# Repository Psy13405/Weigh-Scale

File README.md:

# Custom Portable Weigh Scale

## Overview

Building a custom weigh scale to measure up to 20 kg with high precision. Using a load cell to measure weight and an ESP32C3 development board to send data wirelessly to connected devices and display on LCD module. Modeling the frame of weigh scale in CAD software to 3D print. Designing a PCB to integrate components and optimize space.

## Repository Contents

- `src/` — Source code
- `include/` - Header files for all submodules
- `CAD_Files/` — All CAD models and printable files
- `3D_Prints/` - STL files for physical parts
- `PCB/` - PCB schematic and layout file (in progress)

## Hardware and Software

Hardware: HX711 Amplifier Board, XIAO ESP32C3, Aluminum Bar-type Load Cell, USB Debug Cable, Jumper Wires, 2x M4 and 2x M5 hex screws\
Software: ESP-IDF in preferred configuration. Example: Setup through PlatformIO extension in VS Code\

## Building and Running

Solder load cell wires to HX711 board and use jumper wires to connect to ESP. 3D print test bed and force plate, and fasten them to the load cell with screws. Flash the source code to the ESP and inspect through serial monitor.

## Results

Currently, the load cell reliably measures weight up to 10 kg and sends data wirelessly via Bluetooth Low Energy (BLE). Next steps include integrating an LCD module, modeling the full frame, and finishing the PCB layout for fabrication.

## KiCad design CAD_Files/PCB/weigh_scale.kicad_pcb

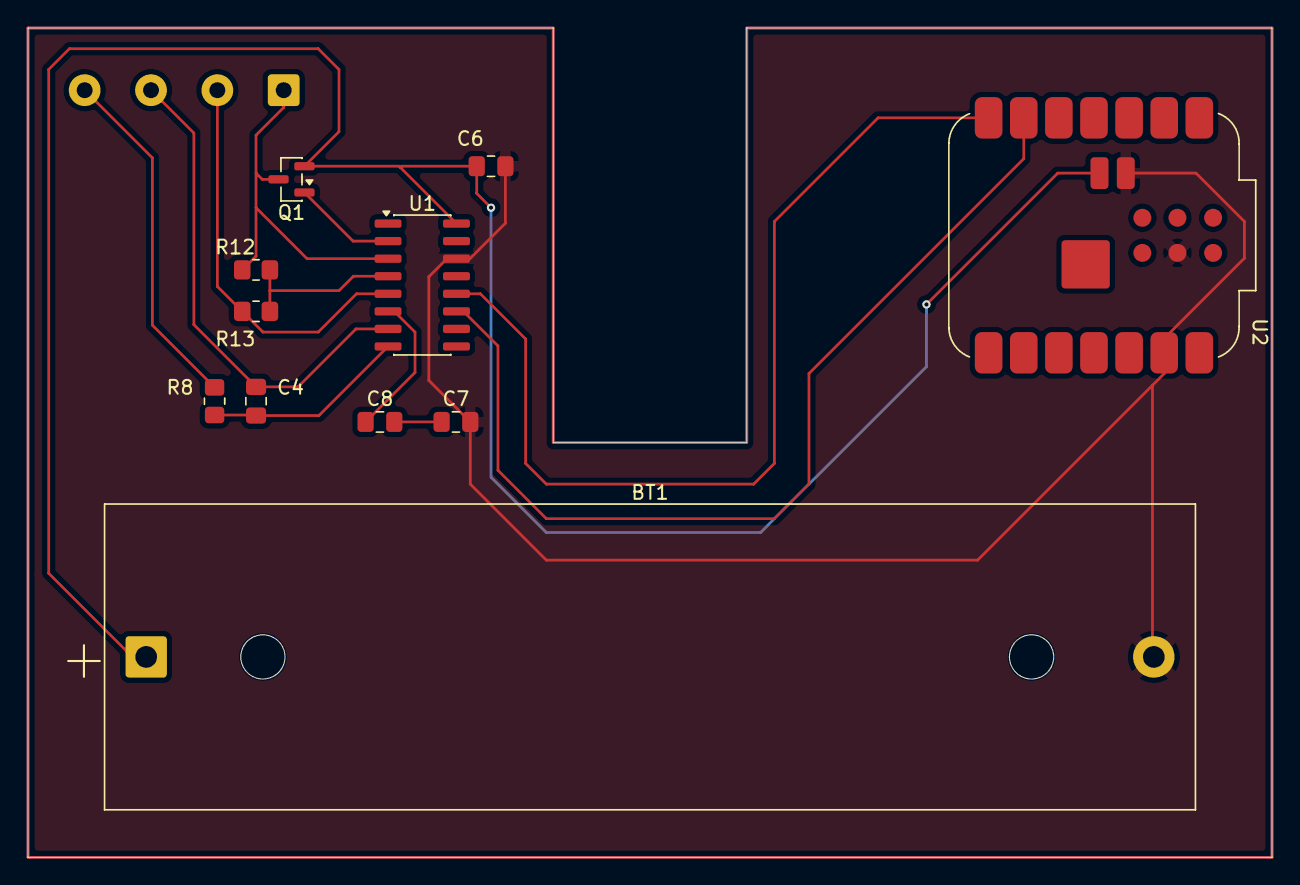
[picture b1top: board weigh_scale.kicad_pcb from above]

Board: 2 copper layers, 90.0 x 60.0 mm, 12 parts (0 on the bottom side), 13 nets.

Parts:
BT1: Battery_Cell; BatteryHolder_MPD_BH-18650-PC
C4, C7, C8: 0.1u; C_0805_2012Metric_Pad1.18x1.45mm_HandSolder
C6: 10u; C_0805_2012Metric_Pad1.18x1.45mm_HandSolder
J1: Conn_01x04_Pin; SolderWire-0.5sqmm_1x04_P4.8mm_D0.9mm_OD2.3mm
Q1: BC856; SOT-23
R8: 1.2k; R_0805_2012Metric_Pad1.20x1.40mm_HandSolder
R12: 20k; R_0805_2012Metric_Pad1.20x1.40mm_HandSolder
R13: 1k; R_0805_2012Metric_Pad1.20x1.40mm_HandSolder
U1: HX711; SOIC-16_3.9x9.9mm_P1.27mm
U2: XIAO-ESP32-C3-SMD; MCU_Seeed_ESP32C3

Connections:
GND: BT1.2 (-), C6.1, C7.2, U1.14 (XI), U2.13 (GND), U2.17 (EN), U2.22 (GND)
unnamed: BT1.1 (+), C6.2, Q1.2 (E), U1.16 (DVDD), U2.16 (D5/MTDO)
unnamed: C7.1, C8.2
unnamed: J1.1, Q1.3 (C), R12.1, U1.3 (AVDD)
unnamed: J1.2, R13.1, U1.5 (AGND)
unnamed: C4.2, J1.3, U1.7 (INA-)
unnamed: J1.4, R8.2
unnamed: Q1.1 (B), U1.2 (BASE)
unnamed: U1.12 (DOUT), U2.7 (D6)
unnamed: C4.1, R8.1, U1.8 (INA+)
unnamed: U1.11 (PD_SCK), U2.6 (D5)
unnamed: C8.1, U1.6 (VBG)
unnamed: R12.2, R13.2, U1.4 (VFB)
